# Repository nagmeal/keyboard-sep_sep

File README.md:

# 作ったキーボード

## [Yubino Hara](https://github.com/nagmeal/sep-sep-kbd/tree/main/yubino-hara)

- 左右分割
- 逆チルト（手前から奥に傾斜）
- シンメトリカルスタッガード
- Remap、VIA対応***予定***

### ファームウェアリポジトリ

https://github.com/nagmeal/qmk_firmware

### 参照・参考ライブラリ

- https://github.com/foostan/kbd
  - シンボル、フットプリント
- https://github.com/daprice/keyswitches.pretty
  - フットプリント
- https://github.com/is-watering/isw-kbd-lib
  - シンボル、フットプリント

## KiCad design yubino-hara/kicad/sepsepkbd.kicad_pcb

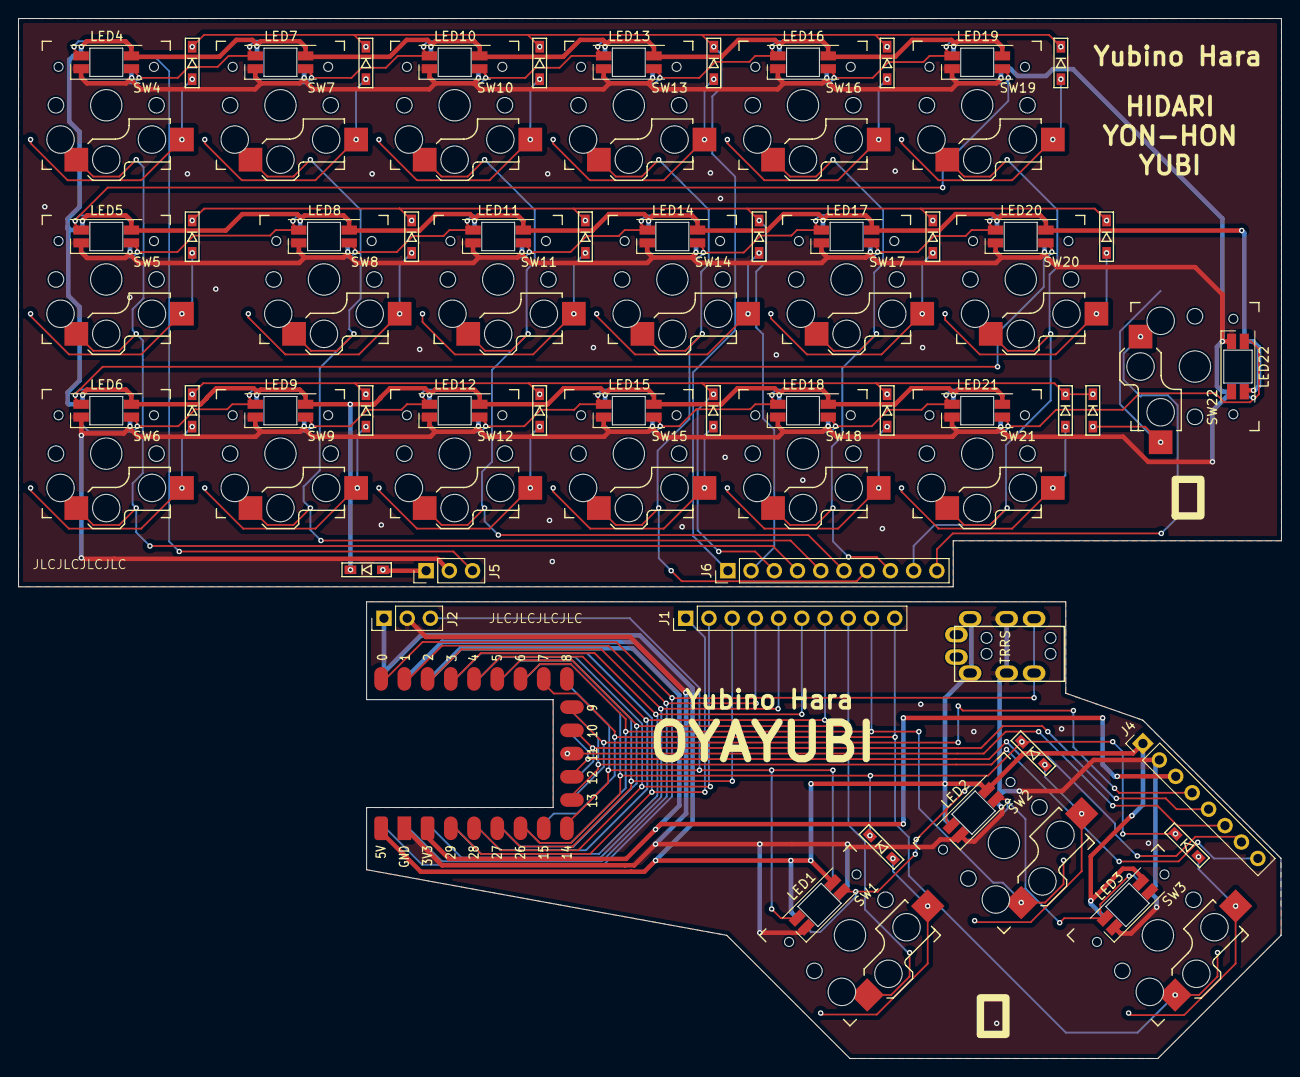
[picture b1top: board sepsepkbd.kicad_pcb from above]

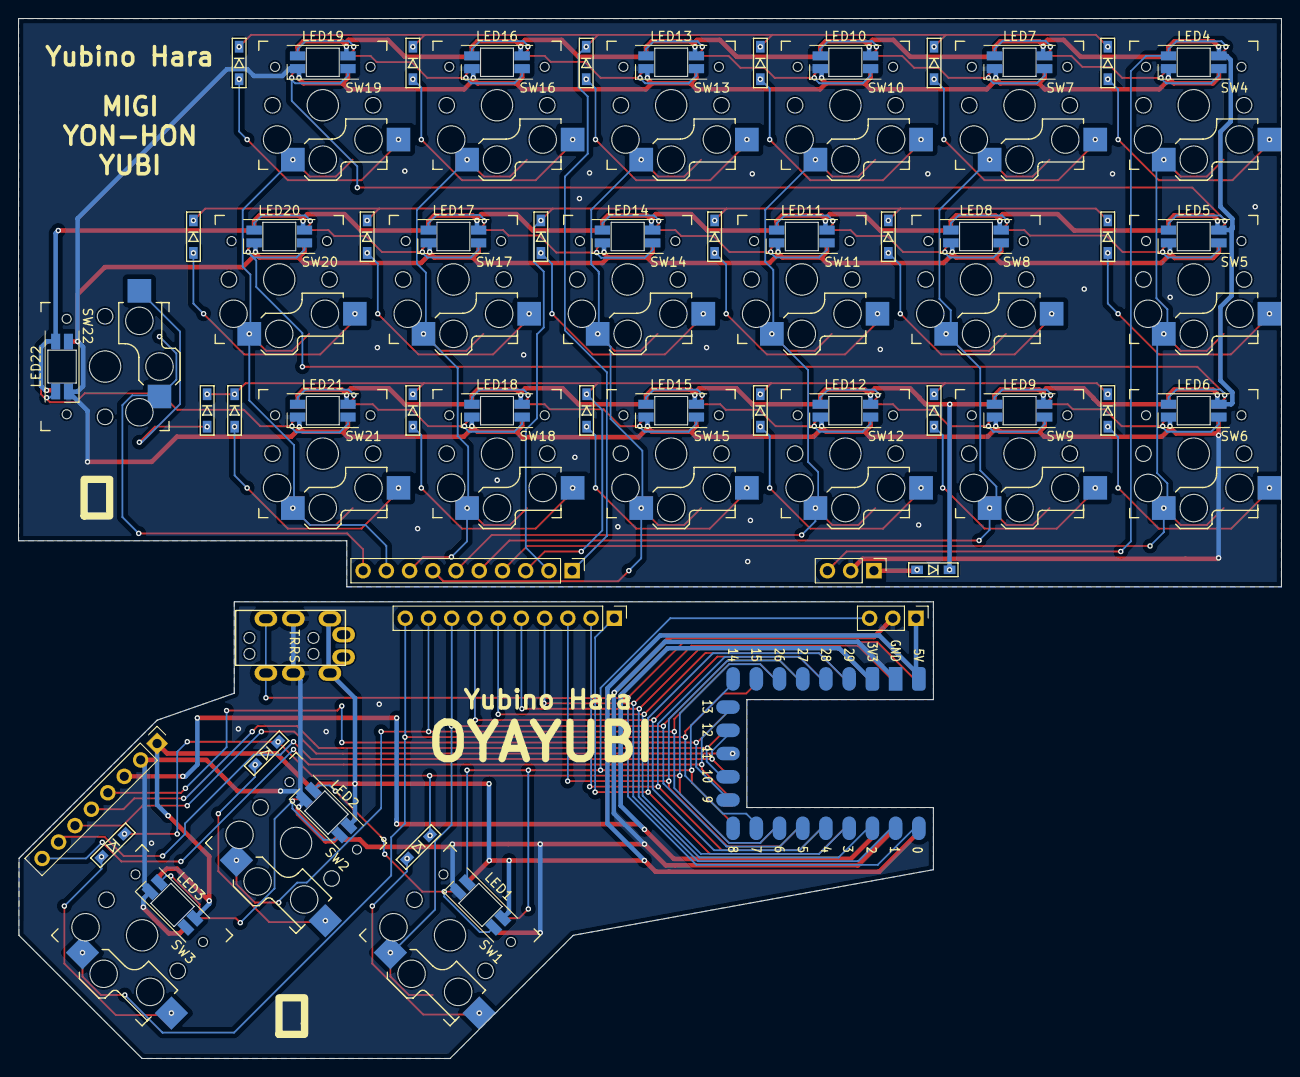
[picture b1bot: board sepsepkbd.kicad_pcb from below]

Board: 2 copper layers, 138.1 x 113.7 mm, 74 parts (3 on the bottom side), 77 nets.

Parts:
D1, D2, D3, D4, D5, D6, D7, D8, D9, D10, D11, D12, D13, D14, D15, D16, D17, D18, D19, D20, D21, D22, D23: D; D3_SMD
J1, J6: Conn_01x10_Pin; PinHeader_1x10_P2.54mm_Vertical
J2, J5: Conn_01x03_Pin; PinHeader_1x03_P2.54mm_Vertical
J3: MJ-4PP-9
J4: Conn_01x08_Pin; PinHeader_1x08_P2.54mm_Vertical
LED1, LED2, LED3, LED4, LED5, LED6, LED7, LED8, LED9, LED10, LED11, LED12, LED13, LED14, LED15, LED16, LED17, LED18, LED19, LED20, LED21, LED22: YS-SK6812MINI-E
SW1, SW2, SW3, SW4, SW5, SW6, SW7, SW8, SW9, SW10, SW11, SW12, SW13, SW14, SW15, SW16, SW17, SW18, SW19, SW20, SW21, SW22: SW_PUSH; Kailh_socket_PG1350_reversible
U1: RP2040-Zero; WS-RP2040-Zero SMD

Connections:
/4Finger/t_col0: J6.4, SW4.1, SW5.1, SW6.1
/4Finger/t_col1: J6.5, SW7.1, SW8.1, SW9.1
/4Finger/t_col2: J6.6, SW10.1, SW11.1, SW12.1
/4Finger/t_col3: J6.7, SW13.1, SW14.1, SW15.1
/4Finger/t_col4: J6.8, SW16.1, SW17.1, SW18.1
/4Finger/t_col5: J6.9, SW19.1, SW20.1, SW21.1
/4Finger/t_col6: J6.10, SW22.1
/4Finger/t_row0: D4.1 (K), D7.1 (K), D10.1 (K), D13.1 (K), D16.1 (K), D19.1 (K), J6.1
/4Finger/t_row1: D5.1 (K), D8.1 (K), D11.1 (K), D14.1 (K), D17.1 (K), D20.1 (K), J6.2
/4Finger/t_row2: D6.1 (K), D9.1 (K), D12.1 (K), D15.1 (K), D18.1 (K), D21.1 (K), D22.1 (K), J6.3
GND: J2.2, J3.C, J4.2, LED1.3 (VSS), LED2.3 (VSS), LED3.3 (VSS), U1.31 (GND)
unnamed: D1.2 (A), SW1.2
unnamed: D2.2 (A), SW2.2
unnamed: D3.2 (A), SW3.2
unnamed: D4.2 (A), SW4.2
unnamed: D5.2 (A), SW5.2
unnamed: D6.2 (A), SW6.2
unnamed: D7.2 (A), SW7.2
unnamed: D8.2 (A), SW8.2
unnamed: D9.2 (A), SW9.2
unnamed: D10.2 (A), SW10.2
unnamed: D11.2 (A), SW11.2
unnamed: D12.2 (A), SW12.2
unnamed: D13.2 (A), SW13.2
unnamed: D14.2 (A), SW14.2
unnamed: D15.2 (A), SW15.2
unnamed: D16.2 (A), SW16.2
unnamed: D17.2 (A), SW17.2
unnamed: D18.2 (A), SW18.2
unnamed: D19.2 (A), SW19.2
unnamed: D20.2 (A), SW20.2
unnamed: D21.2 (A), SW21.2
unnamed: D22.2 (A), SW22.2
unnamed: D23.1 (K), LED4.1 (VDD), LED5.1 (VDD), LED6.1 (VDD), LED7.1 (VDD), LED8.1 (VDD), LED9.1 (VDD), LED10.1 (VDD), LED11.1 (VDD), LED12.1 (VDD), LED13.1 (VDD), LED14.1 (VDD), LED15.1 (VDD), LED16.1 (VDD), LED17.1 (VDD), LED18.1 (VDD), LED19.1 (VDD), LED20.1 (VDD), LED21.1 (VDD), LED22.1 (VDD)
unnamed: LED1.2 (DOUT), LED2.4 (DIN)
unnamed: LED2.2 (DOUT), LED3.4 (DIN)
unnamed: LED4.2 (DOUT), LED7.4 (DIN)
unnamed: LED5.2 (DOUT), LED8.4 (DIN)
unnamed: LED6.2 (DOUT), LED9.4 (DIN)
unnamed: LED7.2 (DOUT), LED10.4 (DIN)
unnamed: LED10.2 (DOUT), LED13.4 (DIN)
unnamed: LED8.2 (DOUT), LED11.4 (DIN)
unnamed: LED11.2 (DOUT), LED14.4 (DIN)
unnamed: LED9.2 (DOUT), LED12.4 (DIN)
unnamed: LED12.2 (DOUT), LED15.4 (DIN)
unnamed: LED13.2 (DOUT), LED16.4 (DIN)
unnamed: LED14.2 (DOUT), LED17.4 (DIN)
unnamed: LED15.2 (DOUT), LED18.4 (DIN)
unnamed: LED16.2 (DOUT), LED19.4 (DIN)
unnamed: LED17.2 (DOUT), LED20.4 (DIN)
unnamed: LED18.2 (DOUT), LED21.4 (DIN)
unnamed: LED5.4 (DIN), LED19.2 (DOUT)
unnamed: LED6.4 (DIN), LED20.2 (DOUT)
unnamed: LED21.2 (DOUT), LED22.4 (DIN)
led: J5.3, LED4.4 (DIN)
t_5v: D23.2 (A), J5.1
t_GND: J5.2, LED4.3 (VSS), LED5.3 (VSS), LED6.3 (VSS), LED7.3 (VSS), LED8.3 (VSS), LED9.3 (VSS), LED10.3 (VSS), LED11.3 (VSS), LED12.3 (VSS), LED13.3 (VSS), LED14.3 (VSS), LED15.3 (VSS), LED16.3 (VSS), LED17.3 (VSS), LED18.3 (VSS), LED19.3 (VSS), LED20.3 (VSS), LED21.3 (VSS), LED22.3 (VSS)
u1_3.3v: J4.3, U1.30 (3V3)
u1_5v: J2.1, J3.D, J4.1, LED1.1 (VDD), LED2.1 (VDD), LED3.1 (VDD), U1.32 (5V)
u1_col0: J1.4, U1.1
u1_col1: J1.5, U1.2
u1_col2: J1.6, U1.3
u1_col3: J1.7, U1.4
u1_col4: J1.8, SW1.1, U1.5
u1_col5: J1.9, SW2.1, U1.6
u1_col6: J1.10, SW3.1, U1.7
u1_data: J3.B, U1.0
u1_led: J2.3, LED1.4 (DIN), U1.14
u1_op1: J4.4, U1.9
u1_op2: J4.5, U1.10
u1_op3: J4.6, U1.11
u1_op4: J4.7, U1.12
u1_op5: J4.8, U1.13
u1_row0: J1.1, U1.29
u1_row1: J1.2, U1.28
u1_row2: J1.3, U1.27
u1_row3: D1.1 (K), D2.1 (K), D3.1 (K), U1.26

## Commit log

2024-04-03 v1.0
2024-04-10 1.01
2024-04-10 手動で追加した裏面シルクをグループ化
2024-04-10 add boy's heart
2024-04-11 adjust diord position
2024-04-22 枠線調整
2024-04-23 フットプリント、シンボル追加。回路図のバージョン情報とキーボード名を変更
2024-04-30 スイッチのズレ修正
2024-05-07 ケース設計用の計測情報を追加
2024-05-07 sep sep -> sprout bird
2024-05-11 2.03
2024-05-24 move trrs to the edge
2024-05-24 2.04
2024-05-24 export step file
2024-05-25 Four-finger boards reduced to the bare minimum
2024-05-25 update ignore
2024-05-26 Split thumbsboard left and right.
2024-05-27 Add LEDs, and convert RP2040 to SMD
2024-06-26 additional silk on both sides
2024-06-26 Cork cutout lines drawn on User3 and User4 layers
2024-06-27 add line for cork
2024-06-27 Reorganized directories
2024-06-27 add Build Guide and firmware
2024-06-27 bugfix
2024-07-02 update documents
2024-07-02 update link
2024-07-03 add case model
2024-08-31 update buildguide
